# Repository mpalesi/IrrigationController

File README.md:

# IrrigationController Firmware

Milestone 1 is an ESP-IDF 5.5.5 foundation for the Freenove FNK0090 `DEV_KIT`.
The application core uses only logical output IDs; board selection happens in the
HAL board-composition layer.

For the DEV_KIT web test, local zones 1-8 use GPIO 16, 17, 18, 19, 21, 22, 23,
and 25 respectively. The development-only Master Valve driver uses GPIO 26.

## Host tests

```sh
cmake -S tests -B build/host-tests
cmake --build build/host-tests
ctest --test-dir build/host-tests --output-on-failure
```

## DEV_KIT build, flash, and monitor

After activating ESP-IDF 5.5.5:

```sh
idf.py -C firmware set-target esp32
idf.py -C firmware build
idf.py -C firmware -p <serial-port> flash monitor
```

`IRRIGATION_CONTROLLER` is intentionally an unconfigured safe placeholder.
It contains no GPIO, MCP23017, relay-channel, or relay-polarity assumptions.

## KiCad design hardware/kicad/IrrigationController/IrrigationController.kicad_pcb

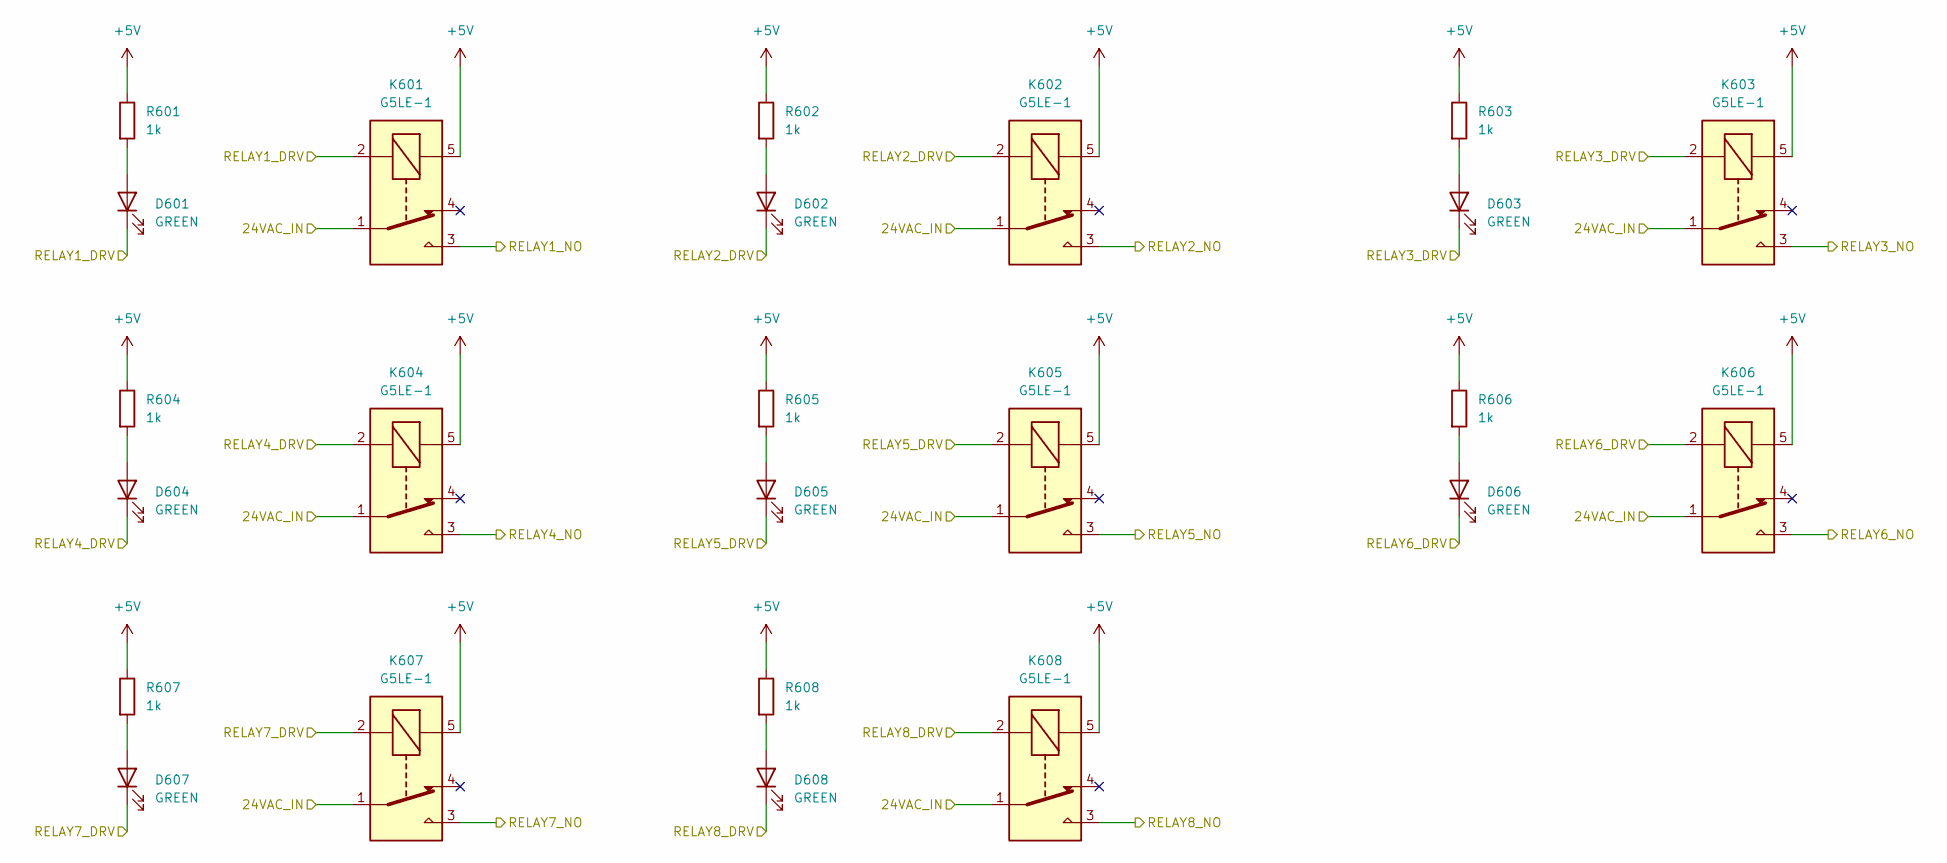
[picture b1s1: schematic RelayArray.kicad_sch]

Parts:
D601, D602, D603, D604, D605, D606, D607, D608: GREEN; C12065_LED0603-RD; LCSC Part # C12065
K601, K602, K603, K604, K605, K606, K607, K608: G5LE-1; C116963_RELAY-TH_G5LE-14-XX; LCSC Part # C116963
R601, R602, R603, R604, R605, R606, R607, R608: 1k; C22548_R0603; LCSC Part # C22548

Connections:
+5V: K601.5, K602.5, K603.5, K604.5, K605.5, K606.5, K607.5, K608.5, R601.1, R602.1, R603.1, R604.1, R605.1, R606.1, R607.1, R608.1; also elsewhere on the board
/Drivers/RELAY1_DRV: D601.1 (K), K601.2; also elsewhere on the board
/Drivers/RELAY2_DRV: D602.1 (K), K602.2; also elsewhere on the board
/Drivers/RELAY3_DRV: D603.1 (K), K603.2; also elsewhere on the board
/Drivers/RELAY4_DRV: D604.1 (K), K604.2; also elsewhere on the board
/Drivers/RELAY5_DRV: D605.1 (K), K605.2; also elsewhere on the board
/Drivers/RELAY6_DRV: D606.1 (K), K606.2; also elsewhere on the board
/Drivers/RELAY7_DRV: D607.1 (K), K607.2; also elsewhere on the board
/Drivers/RELAY8_DRV: D608.1 (K), K608.2; also elsewhere on the board
/RelayArray/24VAC_IN: K601.1, K602.1, K603.1, K604.1, K605.1, K606.1, K607.1, K608.1; also elsewhere on the board
/RelayArray/RELAY1_NO: K601.3; also elsewhere on the board
/RelayArray/RELAY2_NO: K602.3; also elsewhere on the board
/RelayArray/RELAY3_NO: K603.3; also elsewhere on the board
/RelayArray/RELAY4_NO: K604.3; also elsewhere on the board
/RelayArray/RELAY5_NO: K605.3; also elsewhere on the board
/RelayArray/RELAY6_NO: K606.3; also elsewhere on the board
/RelayArray/RELAY7_NO: K607.3; also elsewhere on the board
/RelayArray/RELAY8_NO: K608.3; also elsewhere on the board
unnamed: D601.2 (A), R601.2
unnamed: D602.2 (A), R602.2
unnamed: D603.2 (A), R603.2
unnamed: D604.2 (A), R604.2
unnamed: D605.2 (A), R605.2
unnamed: D606.2 (A), R606.2
unnamed: D607.2 (A), R607.2
unnamed: D608.2 (A), R608.2

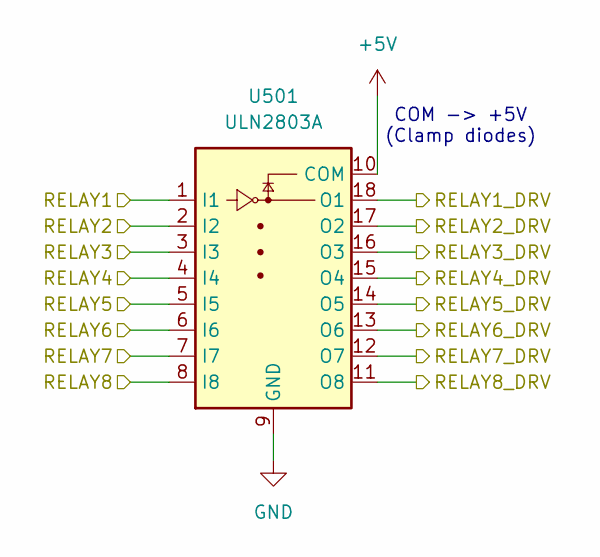
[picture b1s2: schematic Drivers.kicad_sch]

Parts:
U501: ULN2803A; C181731_SOIC-18_L11_6-W7_5-P1_27-LS10_3-BL; LCSC Part # C181731

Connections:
+5V: U501.10 (COM); also elsewhere on the board
/Drivers/RELAY1: U501.1 (I1); also elsewhere on the board
/Drivers/RELAY1_DRV: U501.18 (O1); also elsewhere on the board
/Drivers/RELAY2: U501.2 (I2); also elsewhere on the board
/Drivers/RELAY2_DRV: U501.17 (O2); also elsewhere on the board
/Drivers/RELAY3: U501.3 (I3); also elsewhere on the board
/Drivers/RELAY3_DRV: U501.16 (O3); also elsewhere on the board
/Drivers/RELAY4: U501.4 (I4); also elsewhere on the board
/Drivers/RELAY4_DRV: U501.15 (O4); also elsewhere on the board
/Drivers/RELAY5: U501.5 (I5); also elsewhere on the board
/Drivers/RELAY5_DRV: U501.14 (O5); also elsewhere on the board
/Drivers/RELAY6: U501.6 (I6); also elsewhere on the board
/Drivers/RELAY6_DRV: U501.13 (O6); also elsewhere on the board
/Drivers/RELAY7: U501.7 (I7); also elsewhere on the board
/Drivers/RELAY7_DRV: U501.12 (O7); also elsewhere on the board
/Drivers/RELAY8: U501.8 (I8); also elsewhere on the board
/Drivers/RELAY8_DRV: U501.11 (O8); also elsewhere on the board
GND: U501.9 (GND); also elsewhere on the board

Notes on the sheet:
COM -> +5V (Clamp diodes)

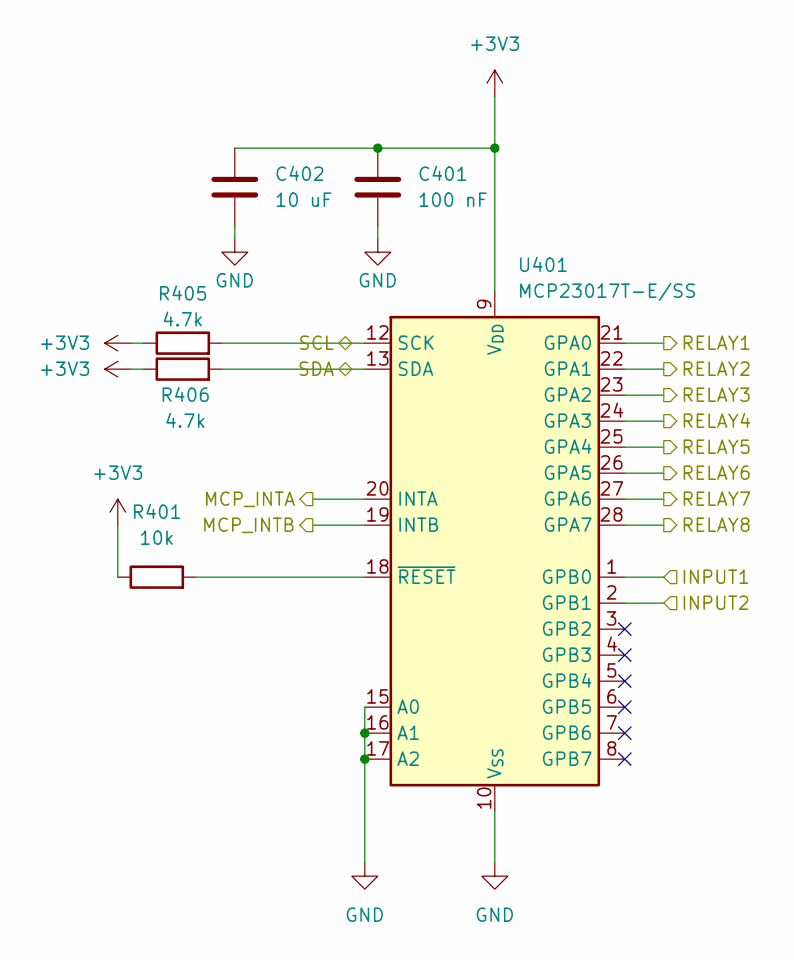
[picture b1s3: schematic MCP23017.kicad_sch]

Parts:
C401: 100 nF; C14663_C0603; LCSC Part # C14663
C402: 10 uF; C13585_C1206; LCSC Part # C13585
R401: 10k; C25804_R0603; LCSC Part # C25804
R405, R406: 4.7k; C23162_R0603; LCSC Part # C23162
U401: MCP23017T-E/SS; C558584_SSOP-28_L10_2-W5_3-P0_65-LS7_8-BL; LCSC Part # C558584

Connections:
+3V3: C401.1, C402.1, R401.1, R405.1, R406.1, U401.9 (V_{DD}); also elsewhere on the board
/Drivers/RELAY1: U401.21 (GPA0); also elsewhere on the board
/Drivers/RELAY2: U401.22 (GPA1); also elsewhere on the board
/Drivers/RELAY3: U401.23 (GPA2); also elsewhere on the board
/Drivers/RELAY4: U401.24 (GPA3); also elsewhere on the board
/Drivers/RELAY5: U401.25 (GPA4); also elsewhere on the board
/Drivers/RELAY6: U401.26 (GPA5); also elsewhere on the board
/Drivers/RELAY7: U401.27 (GPA6); also elsewhere on the board
/Drivers/RELAY8: U401.28 (GPA7); also elsewhere on the board
/ESP32/MCP_INTA: U401.20 (INTA); also elsewhere on the board
/ESP32/MCP_INTB: U401.19 (INTB); also elsewhere on the board
/ESP32/SCL: R405.2, U401.12 (SCK); also elsewhere on the board
/ESP32/SDA: R406.2, U401.13 (SDA); also elsewhere on the board
/MCP23017/INPUT1: U401.1 (GPB0); also elsewhere on the board
/MCP23017/INPUT2: U401.2 (GPB1); also elsewhere on the board
GND: C401.2, C402.2, U401.10 (V_{SS}), U401.15 (A0), U401.16 (A1), U401.17 (A2); also elsewhere on the board
unnamed: R401.2, U401.18 (~RESET)

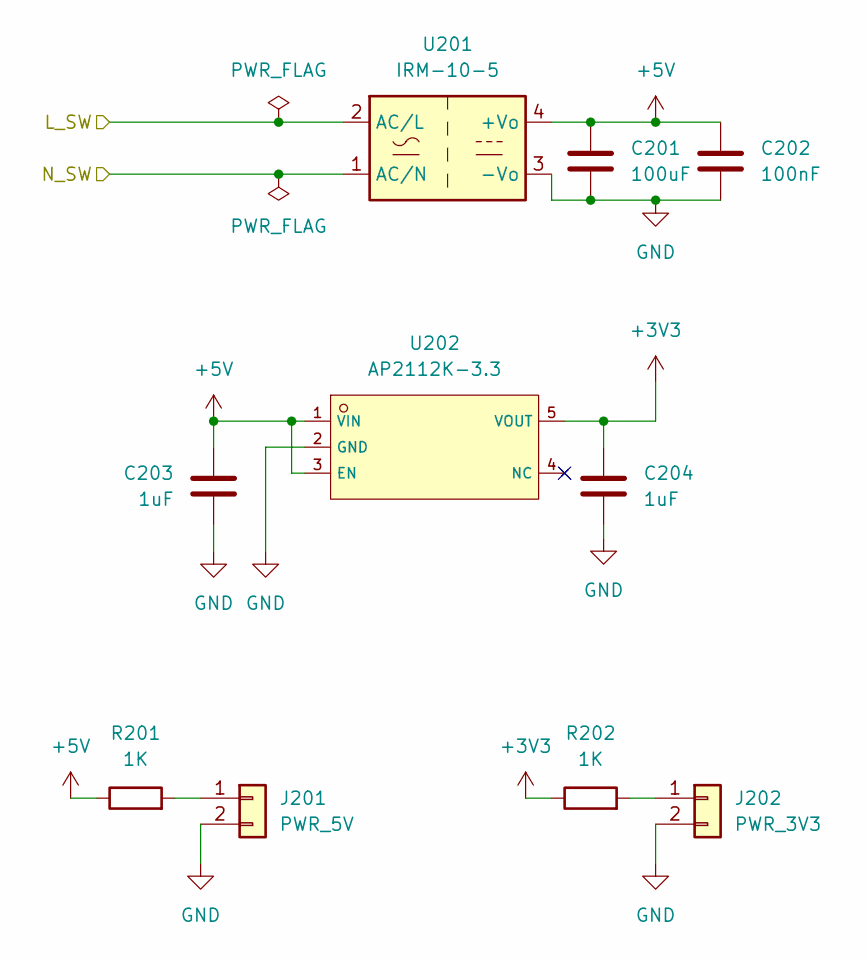
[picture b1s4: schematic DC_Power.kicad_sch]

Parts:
C201: 100uF; C165631_CAP-SMD_BD6_3-L6_6-W6_6-FD; LCSC Part # C165631
C202: 100nF; C14663_C0603; LCSC Part # C14663
C203, C204: 1uF; C15849_C0603; LCSC Part # C15849
J201: PWR_5V; C5360898_HDR-TH_2P-P2_54-V-M-3; LCSC Part # C5360898
J202: PWR_3V3; C5360898_HDR-TH_2P-P2_54-V-M-3; LCSC Part # C5360898
R201, R202: 1K; C22548_R0603; LCSC Part # C22548
U201: IRM-10-5; C2857903_PWRM-TH_4P-L45_7-W25_4-P8_0; LCSC Part # C2857903
U202: AP2112K-3.3; C51118_SOT-25-5_L2_9-W1_6-P0_95-LS2_8-BL; LCSC Part # C51118

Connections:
+3V3: C204.1, R202.1, U202.5 (VOUT); also elsewhere on the board
+5V: C201.1, C202.1, C203.1, R201.1, U201.4 (+Vo), U202.1 (VIN), U202.3 (EN); also elsewhere on the board
/AC_Input/L_SW: U201.2 (AC/L); also elsewhere on the board
/AC_Input/N_SW: U201.1 (AC/N); also elsewhere on the board
GND: C201.2, C202.2, C203.2, C204.2, J201.2, J202.2, U201.3 (-Vo), U202.2 (GND); also elsewhere on the board
unnamed: J201.1, R201.2
unnamed: J202.1, R202.2

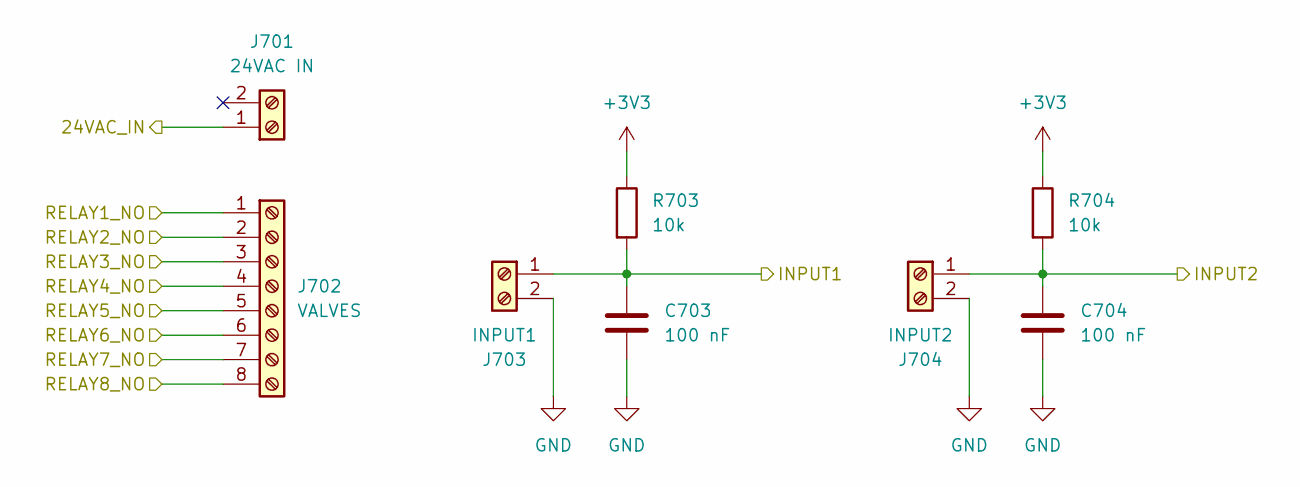
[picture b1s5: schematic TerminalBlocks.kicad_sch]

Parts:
C703, C704: 100 nF; C14663_C0603; LCSC Part # C14663
J701: 24VAC IN; C2915639_CONN-TH_2P-P5_08_DIBO_DB128V-5_08; LCSC Part # C2915639
J702: VALVES; C90065_CONN-TH_8P-P5_08_1757307; LCSC Part # C90065
J703: INPUT1; C2915639_CONN-TH_2P-P5_08_DIBO_DB128V-5_08; LCSC Part # C2915639
J704: INPUT2; C2915639_CONN-TH_2P-P5_08_DIBO_DB128V-5_08; LCSC Part # C2915639
R703, R704: 10k; C25804_R0603; LCSC Part # C25804

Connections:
+3V3: R703.1, R704.1; also elsewhere on the board
/MCP23017/INPUT1: C703.1, J703.1, R703.2; also elsewhere on the board
/MCP23017/INPUT2: C704.1, J704.1, R704.2; also elsewhere on the board
/RelayArray/24VAC_IN: J701.1 (Pin_1_1); also elsewhere on the board
/RelayArray/RELAY1_NO: J702.1; also elsewhere on the board
/RelayArray/RELAY2_NO: J702.2; also elsewhere on the board
/RelayArray/RELAY3_NO: J702.3; also elsewhere on the board
/RelayArray/RELAY4_NO: J702.4; also elsewhere on the board
/RelayArray/RELAY5_NO: J702.5; also elsewhere on the board
/RelayArray/RELAY6_NO: J702.6; also elsewhere on the board
/RelayArray/RELAY7_NO: J702.7; also elsewhere on the board
/RelayArray/RELAY8_NO: J702.8; also elsewhere on the board
GND: C703.2, C704.2, J703.2, J704.2; also elsewhere on the board

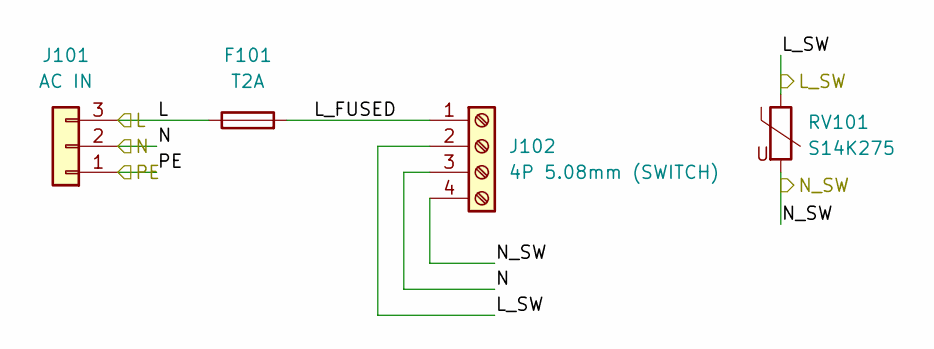
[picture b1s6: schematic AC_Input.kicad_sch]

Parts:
F101: T2A; C3131_FUSE-TH_L22_6-W9_0; LCSC Part # C3131
J101: AC IN; C2915640_CONN-TH_3P-P5_08_DIBO_DB128V-5_08-3P-X; LCSC Part # C2915640
J102: 4P 5.08mm (SWITCH); C2915641_CONN-TH_4P-P5_08_DIBO_DB128V-5_08; LCSC Part # C2915641
RV101: S14K275; C233160_RES-TH_L17_0-W10_0-P7_50-D0_8-S10_00; LCSC Part # C233160

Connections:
/AC_Input/L: F101.1, J101.3
/AC_Input/L_FUSED: F101.2, J102.1
/AC_Input/L_SW: J102.2, RV101.1; also elsewhere on the board
/AC_Input/N: J101.2, J102.3
/AC_Input/N_SW: J102.4, RV101.2; also elsewhere on the board
/AC_Input/PE: J101.1

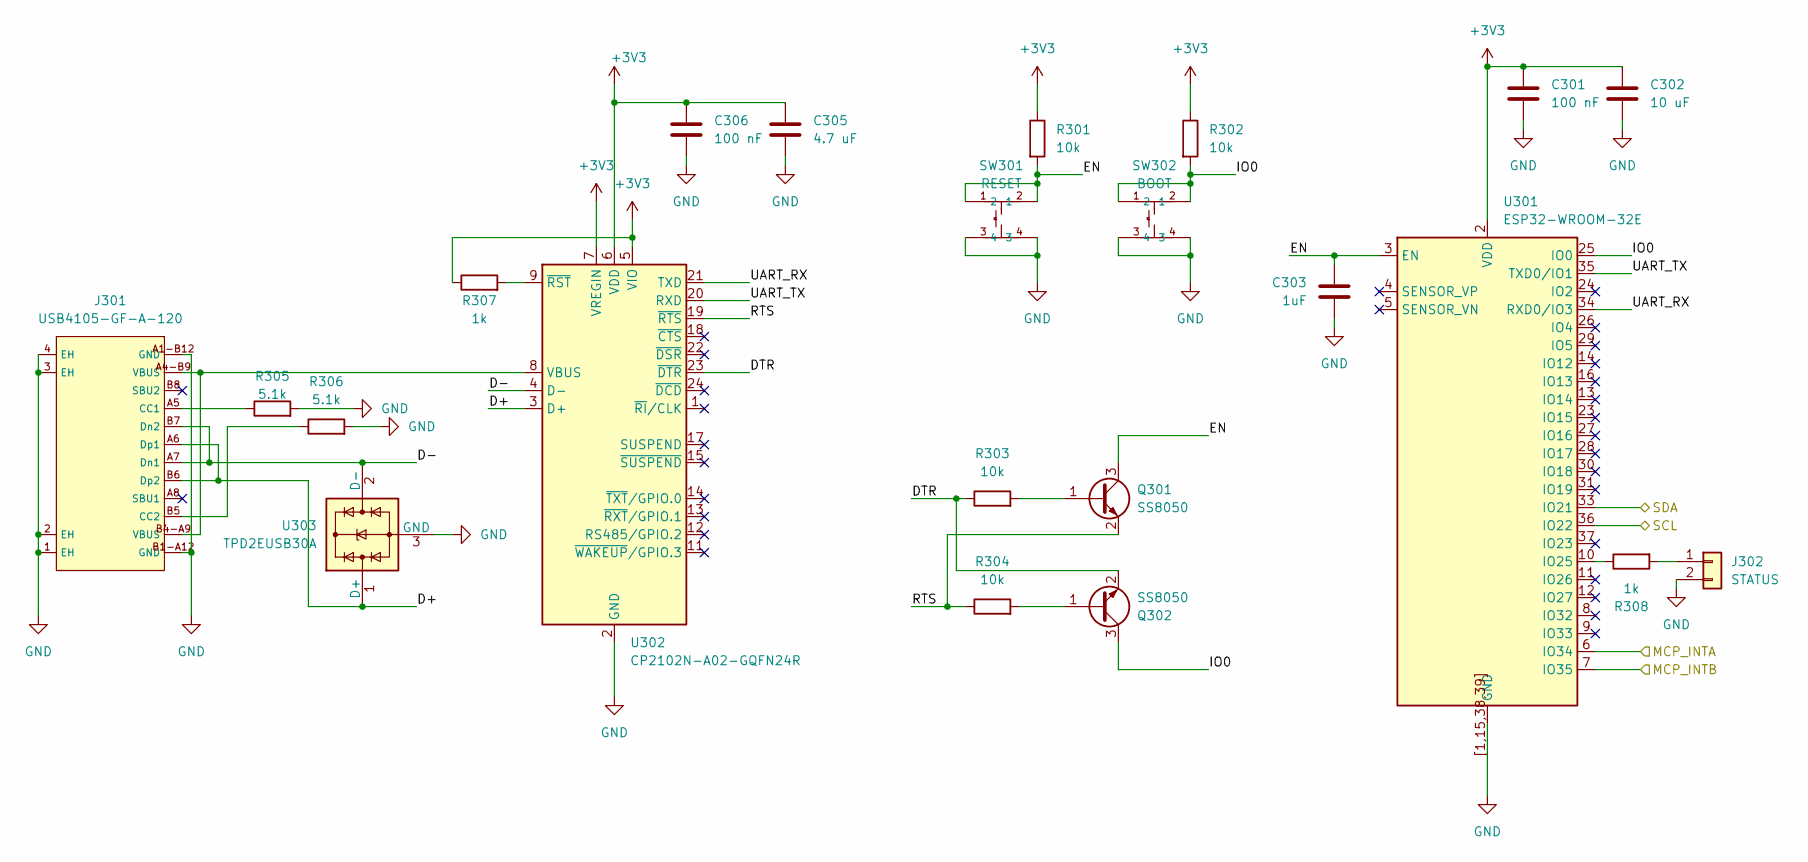
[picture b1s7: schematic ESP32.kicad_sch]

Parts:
C301, C306: 100 nF; C14663_C0603; LCSC Part # C14663
C302: 10 uF; C13585_C1206; LCSC Part # C13585
C303: 1uF; C15849_C0603; LCSC Part # C15849
C305: 4.7 uF; C19666_C0603; LCSC Part # C19666
J301: USB4105-GF-A-120; C5184243_USB-C-SMD_MC-311D; LCSC C5184243
J302: STATUS; C5360898_HDR-TH_2P-P2_54-V-M-3; LCSC Part # C5360898
Q301, Q302: SS8050; C2150_SOT-23-3_L2_9-W1_3-P1_90-LS2_4-BR; LCSC Part # C2150
R301, R302, R303, R304: 10k; C25804_R0603; LCSC Part # C25804
R305, R306: 5.1k; C23186_R0603; LCSC Part # C23186
R307, R308: 1k; C22548_R0603; LCSC Part # C22548
SW301: RESET; C2845315_SW-SMD_4P-L6_0-W6_0-P4_50-LS10_0_TL3301EF160QG; LCSC Part # C2845315
SW302: BOOT; C2845315_SW-SMD_4P-L6_0-W6_0-P4_50-LS10_0_TL3301EF160QG; LCSC Part # C2845315
U301: ESP32-WROOM-32E; C701342_WIFI-SMD_ESP32-WROOM-32E; LCSC Part # C701342
U302: CP2102N-A02-GQFN24R; C969151_QFN-24_L4_0-W4_0-P0_50-TL-EP2_6; LCSC Part # C969151
U303: TPD2EUSB30A; C94934_SOT-9X3-3_L1_0-W0_8-P0_35-LS1_0-BR; LCSC Part # C94934

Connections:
+3V3: C301.1, C302.1, C305.1, C306.1, R301.1, R302.1, R307.1, U301.2 (VDD), U302.5 (VIO), U302.6 (VDD), U302.7 (VREGIN); also elsewhere on the board
/ESP32/D+: J301.A6 (Dp1), J301.B6 (Dp2), U302.3 (D+), U303.1 (D+)
/ESP32/D-: J301.A7 (Dn1), J301.B7 (Dn2), U302.4 (D-), U303.2 (D-)
/ESP32/DTR: Q302.2 (E), R303.1, U302.23 (~DTR)
/ESP32/EN: C303.1, Q301.3 (C), R301.2, SW301.1, SW301.2, U301.3 (EN)
/ESP32/IO0: Q302.3 (C), R302.2, SW302.1, SW302.2, U301.25 (IO0)
/ESP32/MCP_INTA: U301.6 (IO34); also elsewhere on the board
/ESP32/MCP_INTB: U301.7 (IO35); also elsewhere on the board
/ESP32/RTS: Q301.2 (E), R304.1, U302.19 (~RTS)
/ESP32/SCL: U301.36 (IO22); also elsewhere on the board
/ESP32/SDA: U301.33 (IO21); also elsewhere on the board
/ESP32/UART_RX: U301.34 (RXD0/IO3), U302.21 (TXD)
/ESP32/UART_TX: U301.35 (TXD0/IO1), U302.20 (RXD)
GND: C301.2, C302.2, C303.2, C305.2, C306.2, J301.1 (EH), J301.2 (EH), J301.3 (EH), J301.4 (EH), J301.A1-B12 (GND), J301.B1-A12 (GND), J302.2, R305.2, R306.2, SW301.3, SW301.4, SW302.3, SW302.4, U301.1 (GND), U301.15 (GND), U301.38 (GND), U301.39 (GND), U301.[1,15,38,39] (GND), U302.2 (GND), U302.25 (GND), U303.3 (GND); also elsewhere on the board
unnamed: J301.A5 (CC1), R305.1
unnamed: J301.B5 (CC2), R306.1
unnamed: J302.1, R308.2
unnamed: Q301.1 (B), R303.2
unnamed: Q302.1 (B), R304.2
unnamed: R308.1, U301.10 (IO25)
unnamed: J301.A4-B9 (VBUS), J301.B4-A9 (VBUS), U302.8 (VBUS)
unnamed: R307.2, U302.9 (~RST)

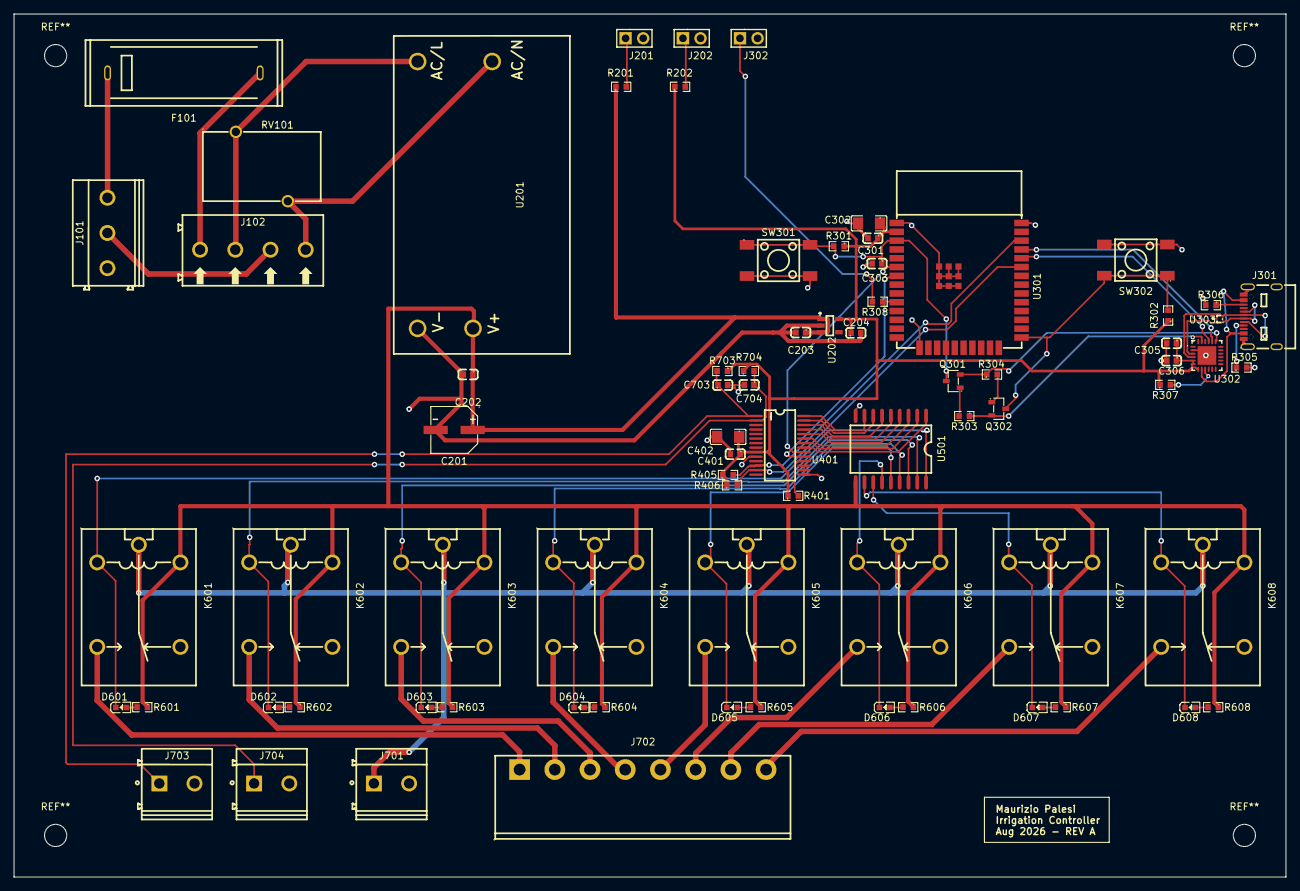
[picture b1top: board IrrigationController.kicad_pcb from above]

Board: 2 copper layers, 183.5 x 124.5 mm, 75 parts (0 on the bottom side), 66 nets.

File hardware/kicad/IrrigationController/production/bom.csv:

Designator,Footprint,Quantity,Value,LCSC Part #
C201,C165631_CAP-SMD_BD6_3-L6_6-W6_6-FD,1,100uF,C165631
C202,C14663_C0603,1,100nF,C14663
"C203, C204, C303",C15849_C0603,3,1uF,C15849
"C301, C306, C401, C703, C704",C14663_C0603,5,100 nF,C14663
"C302, C402",C13585_C1206,2,10 uF,C13585
C305,C19666_C0603,1,4.7 uF,C19666
"D601, D602, D603, D604, D605, D606, D607, D608",C12065_LED0603-RD,8,GREEN,C12065
F101,C3131_FUSE-TH_L22_6-W9_0,1,T2A,C3131
J101,C2915640_CONN-TH_3P-P5_08_DIBO_DB128V-5_08-3P-X,1,AC IN,C2915640
J102,C2915641_CONN-TH_4P-P5_08_DIBO_DB128V-5_08,1,4P 5.08mm (SWITCH),C2915641
J201,C5360898_HDR-TH_2P-P2_54-V-M-3,1,PWR_5V,C5360898
J202,C5360898_HDR-TH_2P-P2_54-V-M-3,1,PWR_3V3,C5360898
J301,C5184243_USB-C-SMD_MC-311D,1,USB4105-GF-A-120,C5184243
J302,C5360898_HDR-TH_2P-P2_54-V-M-3,1,STATUS,C5360898
J701,C2915639_CONN-TH_2P-P5_08_DIBO_DB128V-5_08,1,24VAC IN,C2915639
J702,C90065_CONN-TH_8P-P5_08_1757307,1,VALVES,C90065
J703,C2915639_CONN-TH_2P-P5_08_DIBO_DB128V-5_08,1,INPUT1,C2915639
J704,C2915639_CONN-TH_2P-P5_08_DIBO_DB128V-5_08,1,INPUT2,C2915639
"K601, K602, K603, K604, K605, K606, K607, K608",C116963_RELAY-TH_G5LE-14-XX,8,G5LE-1,C116963
"Q301, Q302",C2150_SOT-23-3_L2_9-W1_3-P1_90-LS2_4-BR,2,SS8050,C2150
"R201, R202, R307, R308, R601, R602, R603, R604, R605, R606, R607, R608",C22548_R0603,12,1K,C22548
"R301, R302, R303, R304, R401, R703, R704",C25804_R0603,7,10k,C25804
"R305, R306",C23186_R0603,2,5.1k,C23186
"R405, R406",C23162_R0603,2,4.7k,C23162
RV101,C233160_RES-TH_L17_0-W10_0-P7_50-D0_8-S10_00,1,S14K275,C233160
SW301,C2845315_SW-SMD_4P-L6_0-W6_0-P4_50-LS10_0_TL3301EF160QG,1,RESET,C2845315
SW302,C2845315_SW-SMD_4P-L6_0-W6_0-P4_50-LS10_0_TL3301EF160QG,1,BOOT,C2845315
U201,C2857903_PWRM-TH_4P-L45_7-W25_4-P8_0,1,IRM-10-5,C2857903
U202,C51118_SOT-25-5_L2_9-W1_6-P0_95-LS2_8-BL,1,AP2112K-3.3,C51118
U301,C701342_WIFI-SMD_ESP32-WROOM-32E,1,ESP32-WROOM-32E,C701342
U302,C969151_QFN-24_L4_0-W4_0-P0_50-TL-EP2_6,1,CP2102N-A02-GQFN24R,C969151
U303,C94934_SOT-9X3-3_L1_0-W0_8-P0_35-LS1_0-BR,1,TPD2EUSB30A,C94934
U401,C558584_SSOP-28_L10_2-W5_3-P0_65-LS7_8-BL,1,MCP23017T-E/SS,C558584
U501,C181731_SOIC-18_L11_6-W7_5-P1_27-LS10_3-BL,1,ULN2803A,C181731
